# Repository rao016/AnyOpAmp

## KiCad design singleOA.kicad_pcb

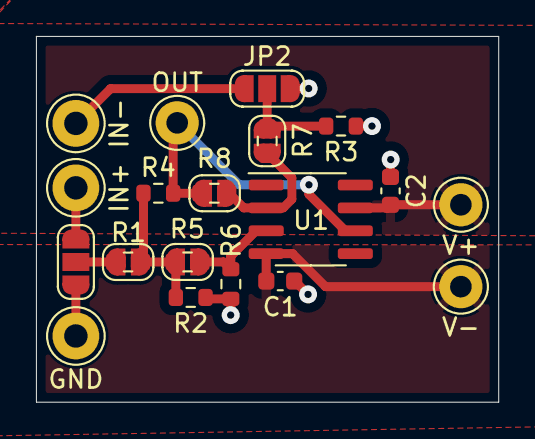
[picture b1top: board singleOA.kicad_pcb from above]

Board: 2 copper layers, 25.7 x 20.3 mm, 23 parts (0 on the bottom side), 11 nets.

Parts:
C1, C2: C; C_0603_1608Metric
GND: Conn_01x01_Female; Pin_D1.3mm_L11.0mm
IN+: Conn_01x01_Female; Pin_D1.3mm_L11.0mm
IN-: Conn_01x01_Female; Pin_D1.3mm_L11.0mm
JP1, JP2: SolderJumper_3_Open; SolderJumper-3_P1.3mm_Open_RoundedPad1.0x1.5mm_NumberLabels
JP3, JP4, JP5, JP6: SolderJumper_2_Open; SolderJumper-2_P1.3mm_Open_RoundedPad1.0x1.5mm
OUT: Conn_01x01_Female; Pin_D1.0mm_L10.0mm_LooseFit
R1, R2, R3, R4, R5, R6, R7, R8: R; R_0603_1608Metric
U1: OPA333xxD; SOIC-8_3.9x4.9mm_P1.27mm
V+: Conn_01x01_Female; Pin_D1.0mm_L10.0mm_LooseFit
V-: Conn_01x01_Female; Pin_D1.0mm_L10.0mm_LooseFit

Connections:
GND: C1.1, C2.1, GND.1, JP1.1 (A), JP2.3 (B), R2.1, R3.1, R6.1
unnamed: IN-.1, JP2.1 (A)
unnamed: JP1.2 (C), JP3.1 (A), R1.1
unnamed: IN+.1, JP1.3 (B)
unnamed: JP2.2 (C), JP5.1 (A), R3.2, R7.1
unnamed: JP3.2 (B), JP4.1 (A), R1.2, R2.2, R4.1, R5.1
unnamed: JP4.2 (B), R5.2, R6.2, U1.3 (+)
unnamed: JP5.2 (B), JP6.1 (A), R7.2, R8.1, U1.2 (-)
unnamed: JP6.2 (B), OUT.1, R4.2, R8.2, U1.6
VCC: C2.2, U1.7 (V+), V+.1
VSS: C1.2, U1.4 (V-), V-.1

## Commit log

2022-01-29 Single OpAmp Made
